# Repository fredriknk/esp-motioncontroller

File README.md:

# esp-motioncontroller

 <!-- 3D rendered pretty view -->

INFO INFO

[PCB layout](./DOCUMENTATION/esp-motioncontroller_board_prints.pdf) <!-- PDFs of boards -->
[SCHEMATIC](./DOCUMENTATION/esp-motioncontroller_schematic.pdf) <!-- Schematic PDFs -->

## FRONT

## BACK

## SIDE

# Before major commmits
Remember to run generate_outputs.bat/sh
to update the outputs and pictures.
readmetemplate

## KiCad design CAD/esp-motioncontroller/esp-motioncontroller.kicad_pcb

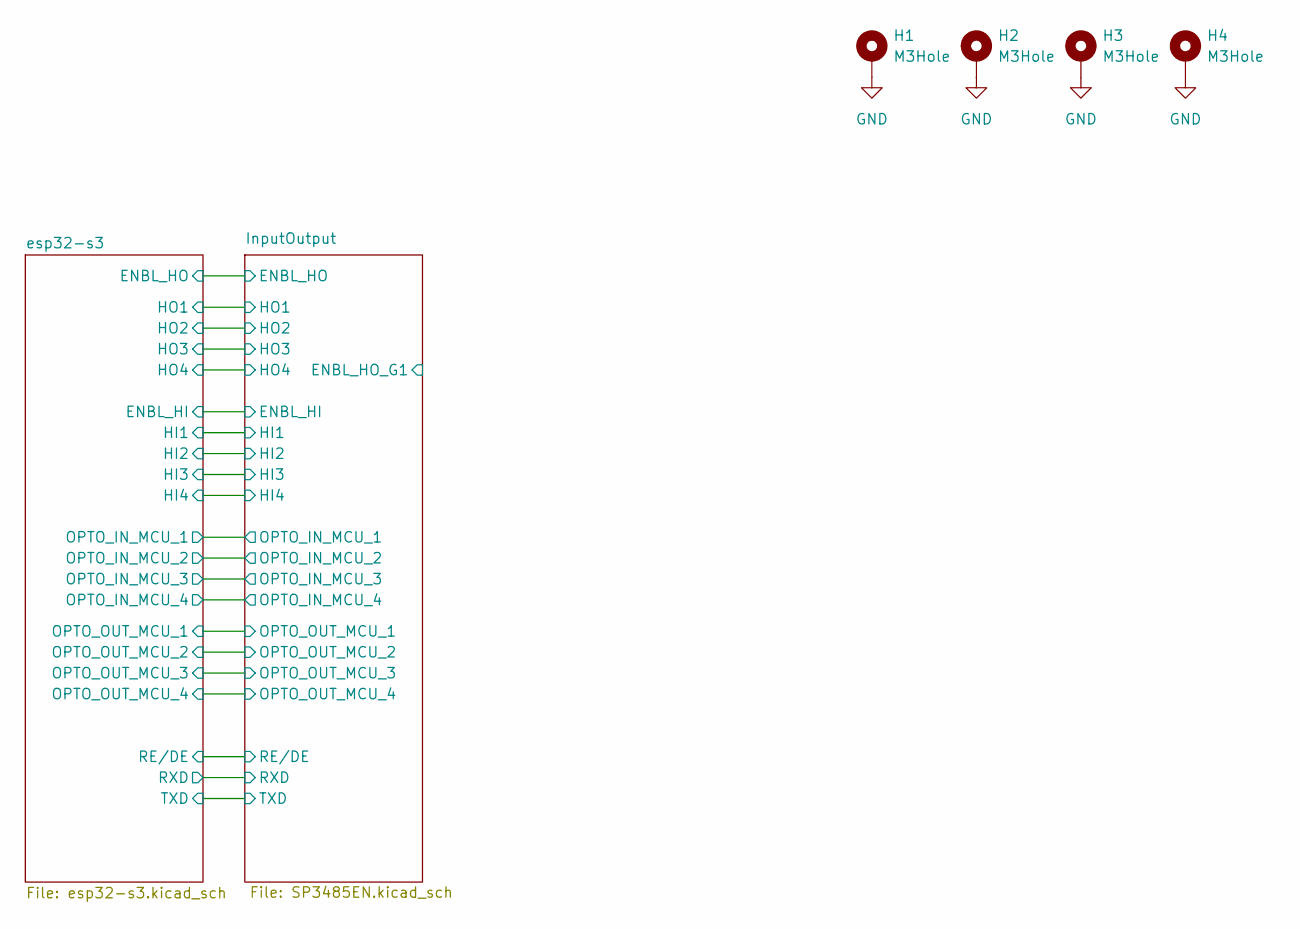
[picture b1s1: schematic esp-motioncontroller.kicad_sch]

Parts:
H1, H2, H3, H4: M3Hole; MountingHole_3.2mm_M3_DIN965_Pad

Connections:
GND: H1.1, H2.1, H3.1, H4.1; also elsewhere on the board

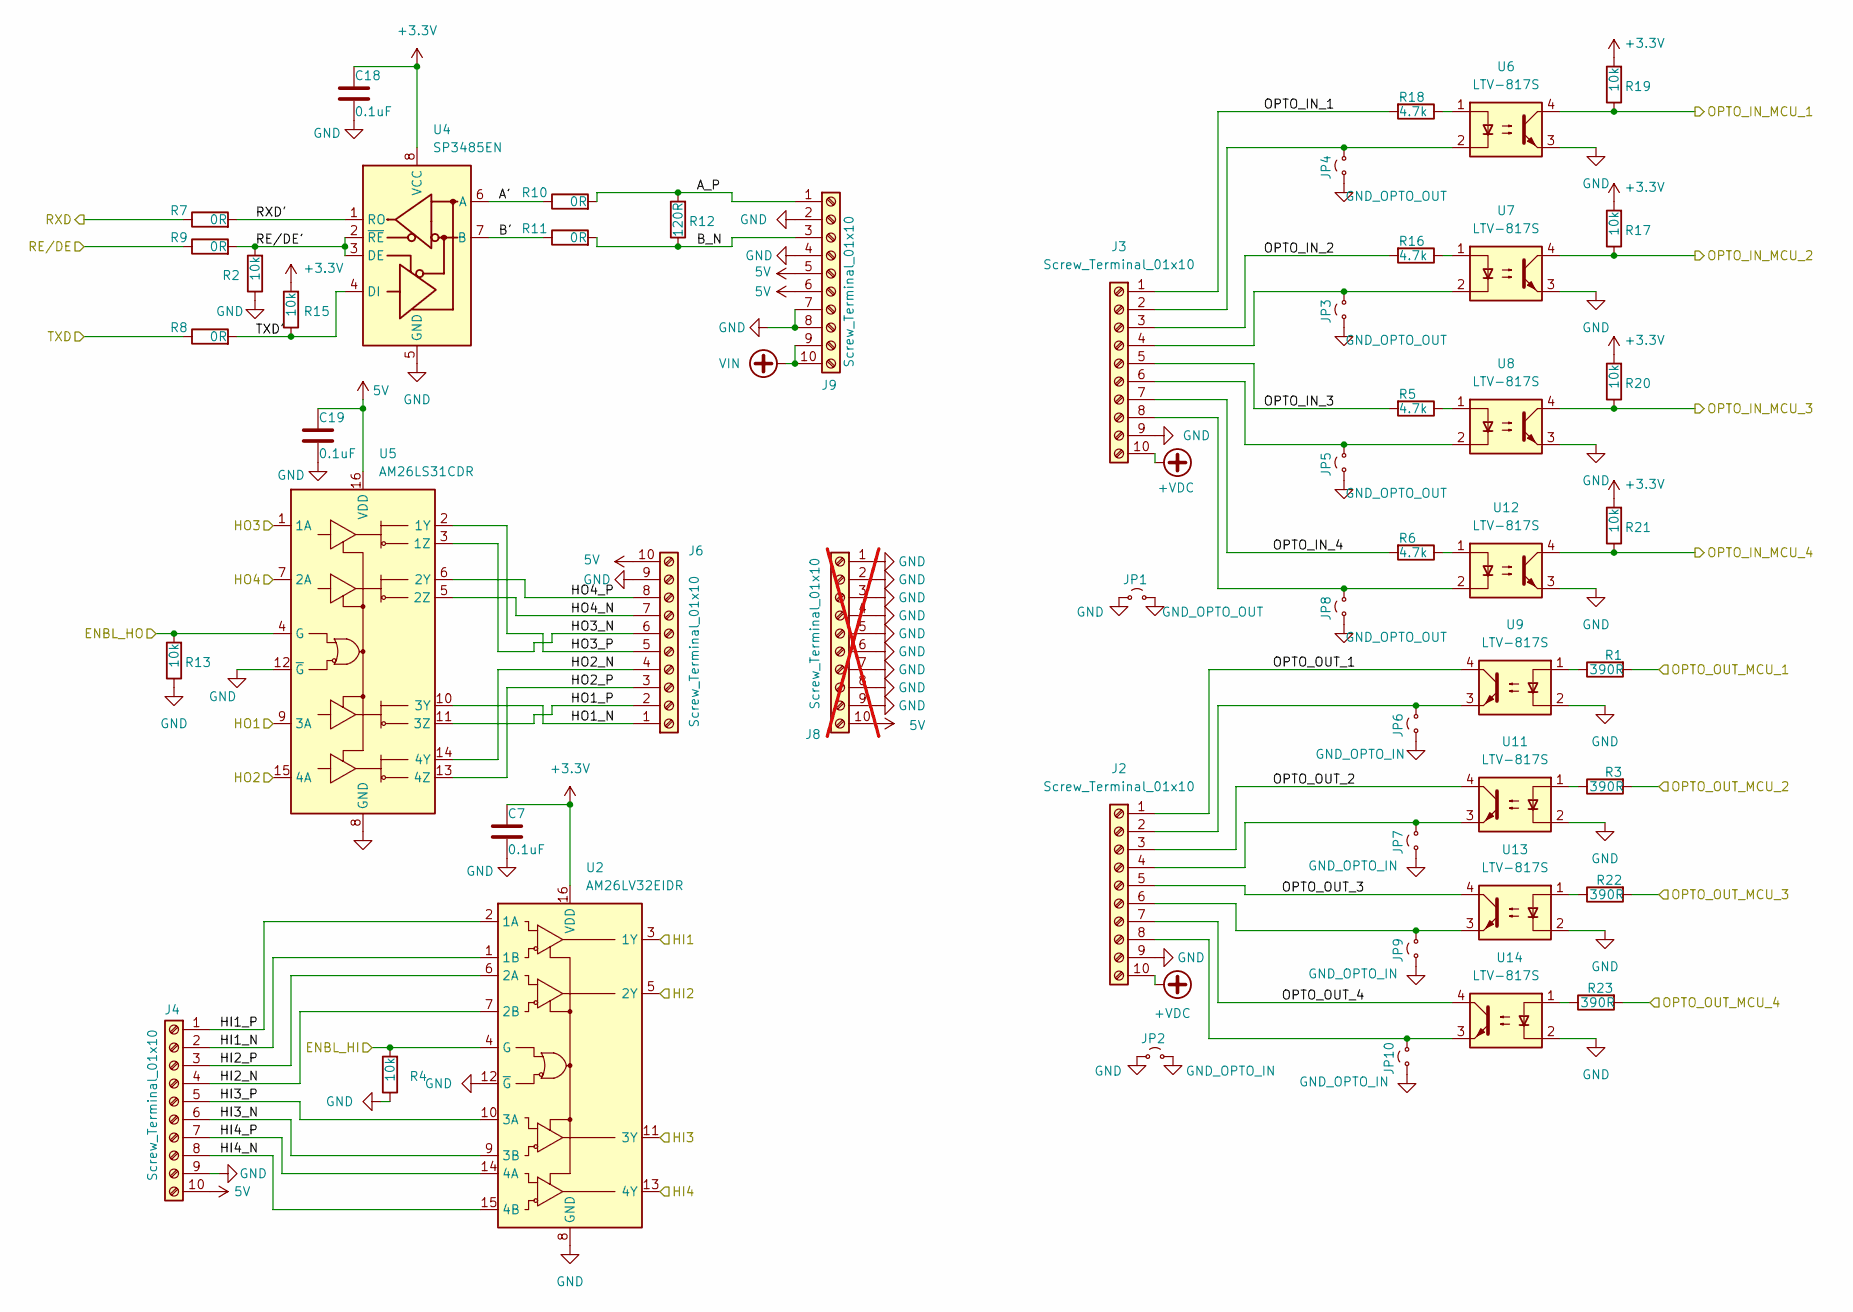
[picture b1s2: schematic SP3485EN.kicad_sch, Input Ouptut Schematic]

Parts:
C7, C18, C19: 0.1uF; C_0603_1608Metric; LCSC C14663
J2, J3, J4, J6, J9: Screw_Terminal_01x10; TerminalBlock_Phoenix_PT-1,5-10-3.5-H_1x10_P3.50mm_Horizont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; LCSC C5184956
J8: Screw_Terminal_01x10; TerminalBlock_Phoenix_PT-1,5-10-3.5-H_1x10_P3.50mm_Horizont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; LCSC C5184956; not fitted
JP1, JP2, JP3, JP4, JP5, JP6, JP7, JP8, JP9, JP10: Jumper_2_Small_Open; TestPoint_2Pads_Pitch2.54mm_Drill0.8mm
R1, R3, R22, R23: 390R; R_0603_1608Metric; LCSC C23151
R2, R4, R13, R15, R17, R19, R20, R21: 10k; R_0603_1608Metric; LCSC C25804
R5, R6, R16, R18: 4.7k; R_0603_1608Metric; LCSC C23162
R7, R8, R9, R10, R11: 0R; R_0603_1608Metric; LCSC C17477
R12: 120R; R_0603_1608Metric; LCSC C22787
U2: AM26LV32EIDR; SOIC-16_3.9x9.9mm_P1.27mm; LCSC C527448
U4: SP3485EN; SOIC-8_3.9x4.9mm_P1.27mm; LCSC C8963
U5: AM26LS31CDR; SOIC-16_3.9x9.9mm_P1.27mm; LCSC C6179
U6, U7, U8, U9, U11, U12, U13, U14: LTV-817S; SMDIP-4_W9.53mm; LCSC C109227

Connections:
5V: C19.1, J4.10, J6.10, J8.10, J9.5, J9.6, U5.16 (VDD); also elsewhere on the board
+3.3V: C7.1, C18.1, R15.2, R17.2, R19.2, R20.2, R21.2, U2.16 (VDD), U4.8 (VCC); also elsewhere on the board
+VDC: J2.10, J3.10; also elsewhere on the board
/InputOutput/A': R10.1, U4.6 (A)
/InputOutput/A_P: J9.1, R10.2, R12.2
/InputOutput/B': R11.1, U4.7 (B)
/InputOutput/B_N: J9.3, R11.2, R12.1
/InputOutput/ENBL_HI: R4.2, U2.4 (G); also elsewhere on the board
/InputOutput/ENBL_HO: R13.2, U5.4 (G); also elsewhere on the board
/InputOutput/HI1: U2.3 (1Y); also elsewhere on the board
/InputOutput/HI1_N: J4.2, U2.1 (1B)
/InputOutput/HI1_P: J4.1, U2.2 (1A)
/InputOutput/HI2: U2.5 (2Y); also elsewhere on the board
/InputOutput/HI2_N: J4.4, U2.7 (2B)
/InputOutput/HI2_P: J4.3, U2.6 (2A)
/InputOutput/HI3: U2.11 (3Y); also elsewhere on the board
/InputOutput/HI3_N: J4.6, U2.9 (3B)
/InputOutput/HI3_P: J4.5, U2.10 (3A)
/InputOutput/HI4: U2.13 (4Y); also elsewhere on the board
/InputOutput/HI4_N: J4.8, U2.15 (4B)
/InputOutput/HI4_P: J4.7, U2.14 (4A)
/InputOutput/HO1: U5.9 (3A); also elsewhere on the board
/InputOutput/HO1_N: J6.1, U5.10 (3Y)
/InputOutput/HO1_P: J6.2, U5.11 (3Z)
/InputOutput/HO2: U5.15 (4A); also elsewhere on the board
/InputOutput/HO2_N: J6.4, U5.14 (4Y)
/InputOutput/HO2_P: J6.3, U5.13 (4Z)
/InputOutput/HO3: U5.1 (1A); also elsewhere on the board
/InputOutput/HO3_N: J6.6, U5.3 (1Z)
/InputOutput/HO3_P: J6.5, U5.2 (1Y)
/InputOutput/HO4: U5.7 (2A); also elsewhere on the board
/InputOutput/HO4_N: J6.7, U5.5 (2Z)
/InputOutput/HO4_P: J6.8, U5.6 (2Y)
/InputOutput/OPTO_IN_1: J3.1, R18.2
/InputOutput/OPTO_IN_2: J3.3, R16.2
/InputOutput/OPTO_IN_3: J3.5, R5.2
/InputOutput/OPTO_IN_4: J3.7, R6.2
/InputOutput/OPTO_IN_MCU_1: R19.1, U6.4; also elsewhere on the board
/InputOutput/OPTO_IN_MCU_2: R17.1, U7.4; also elsewhere on the board
/InputOutput/OPTO_IN_MCU_3: R20.1, U8.4; also elsewhere on the board
/InputOutput/OPTO_IN_MCU_4: R21.1, U12.4; also elsewhere on the board
/InputOutput/OPTO_OUT_1: J2.1, U9.4
/InputOutput/OPTO_OUT_2: J2.3, U11.4
/InputOutput/OPTO_OUT_3: J2.5, U13.4
/InputOutput/OPTO_OUT_4: J2.7, U14.4
/InputOutput/OPTO_OUT_MCU_1: R1.2; also elsewhere on the board
/InputOutput/OPTO_OUT_MCU_2: R3.2; also elsewhere on the board
/InputOutput/OPTO_OUT_MCU_3: R22.2; also elsewhere on the board
/InputOutput/OPTO_OUT_MCU_4: R23.2; also elsewhere on the board
/InputOutput/RE/DE: R9.1; also elsewhere on the board
/InputOutput/RE/DE': R2.2, R9.2, U4.2 (~RE), U4.3 (DE)
/InputOutput/RXD: R7.1; also elsewhere on the board
/InputOutput/RXD': R7.2, U4.1 (RO)
/InputOutput/TXD: R8.1; also elsewhere on the board
/InputOutput/TXD': R8.2, R15.1, U4.4 (DI)
GND: C7.2, C18.2, C19.2, J2.9, J3.9, J4.9, J6.9, J8.1, J8.2, J8.3, J8.4, J8.5, J8.6, J8.7, J8.8, J8.9, J9.2, J9.4, J9.7, J9.8, JP1.1 (A), JP2.1 (A), R2.1, R4.1, R13.1, U2.8 (GND), U2.12 (~G), U4.5 (GND), U5.8 (GND), U5.12 (~G), U6.3, U7.3, U8.3, U9.2, U11.2, U12.3, U13.2, U14.2; also elsewhere on the board
GND_OPTO_IN: JP2.2 (B), JP6.1 (A), JP7.1 (A), JP9.1 (A), JP10.1 (A)
GND_OPTO_OUT: JP1.2 (B), JP3.1 (A), JP4.1 (A), JP5.1 (A), JP8.1 (A)
unnamed: J2.2, JP6.2 (B), U9.3
unnamed: J2.4, JP7.2 (B), U11.3
unnamed: J2.6, JP9.2 (B), U13.3
unnamed: J2.8, JP10.2 (B), U14.3
unnamed: J3.2, JP4.2 (B), U6.2
unnamed: J3.4, JP3.2 (B), U7.2
unnamed: J3.6, JP5.2 (B), U8.2
unnamed: J3.8, JP8.2 (B), U12.2
unnamed: R1.1, U9.1
unnamed: R3.1, U11.1
unnamed: R5.1, U8.1
unnamed: R6.1, U12.1
unnamed: R16.1, U7.1
unnamed: R18.1, U6.1
unnamed: R22.1, U13.1
unnamed: R23.1, U14.1
VIN: J9.9, J9.10; also elsewhere on the board

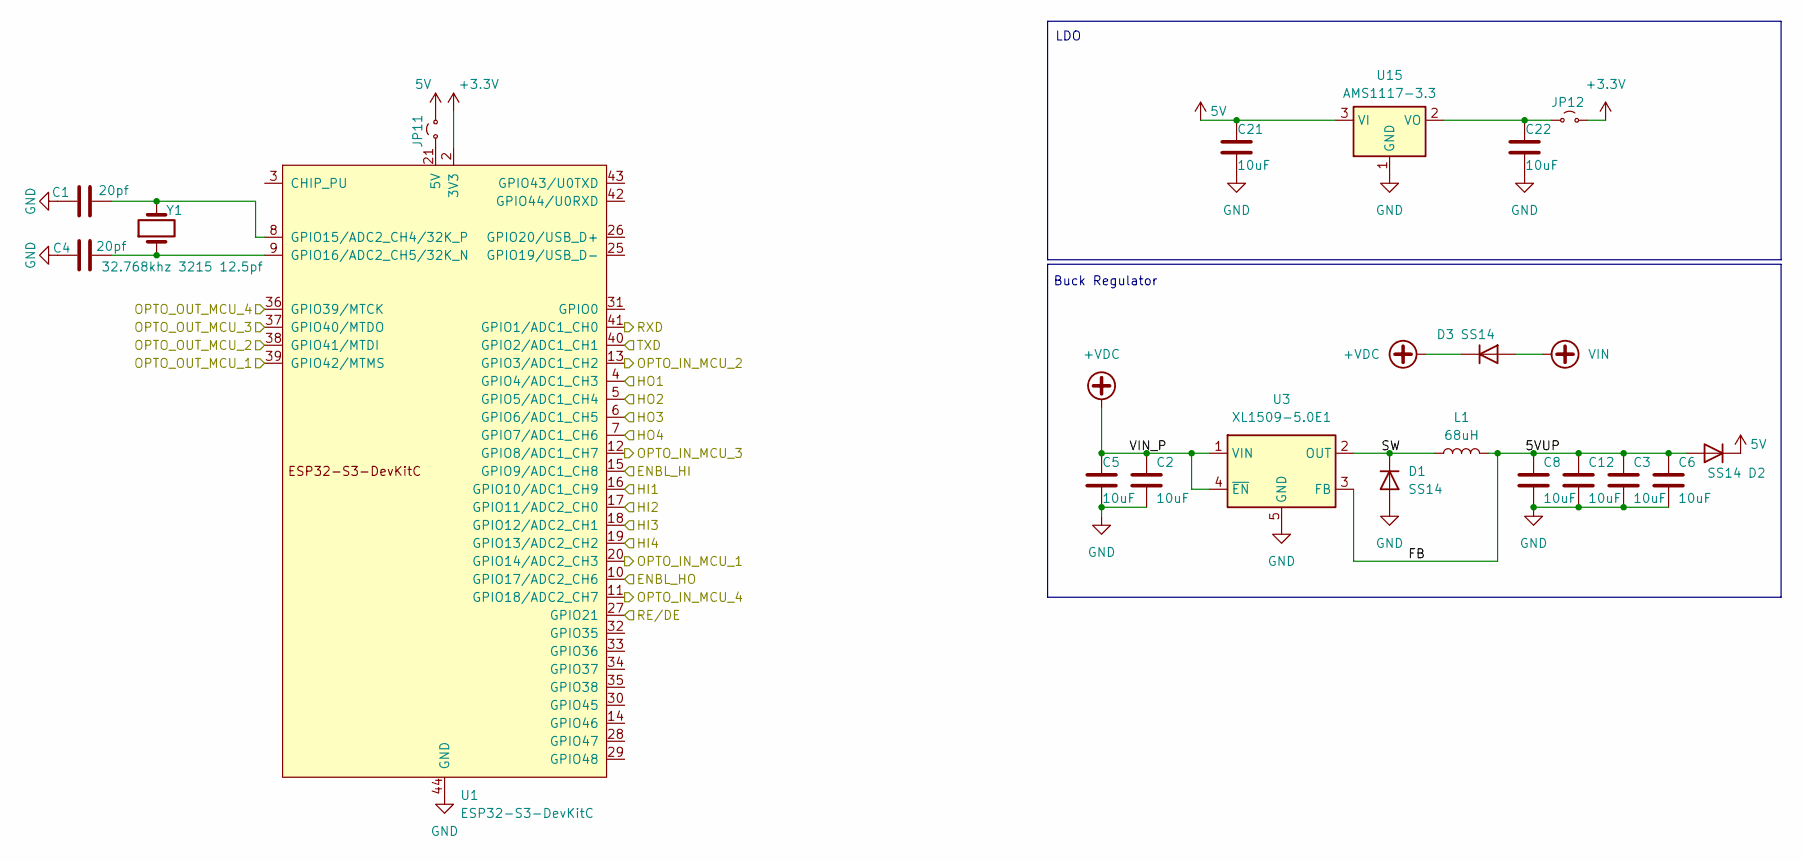
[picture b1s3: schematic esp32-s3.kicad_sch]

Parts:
C1, C4: 20pf; R_0603_1608Metric; LCSC C1648
C2, C3, C5, C6, C8, C12, C21, C22: 10uF; C_1206_3216Metric; LCSC C13585
D1, D2, D3: SS14; D_SMA; LCSC C2480
JP11, JP12: Jumper_2_Small_Open; TestPoint_2Pads_Pitch2.54mm_Drill0.8mm
L1: 68uH; L_SOREDE_SNR.1050_10x10x5mm; LCSC C9187
U1: ESP32-S3-DevKitC
U3: XL1509-5.0E1; SOIC-8_3.9x4.9mm_P1.27mm; LCSC C61063
U15: AMS1117-3.3; SOT-223-3_TabPin2; LCSC C6186
Y1: 32.768khz 3215 12.5pf; Crystal_SMD_3215-2Pin_3.2x1.5mm; LCSC C32346

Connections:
5V: C21.1, D2.1 (K), JP11.2 (B), U15.3 (VI); also elsewhere on the board
+3.3V: JP12.2 (B), U1.1 (3V3), U1.2 (3V3); also elsewhere on the board
+VDC: C2.1, C5.1, D3.1 (K), U3.1 (VIN), U3.4 (~EN); also elsewhere on the board
/InputOutput/ENBL_HI: U1.15 (GPIO9/ADC1_CH8); also elsewhere on the board
/InputOutput/ENBL_HO: U1.10 (GPIO17/ADC2_CH6); also elsewhere on the board
/InputOutput/HI1: U1.16 (GPIO10/ADC1_CH9); also elsewhere on the board
/InputOutput/HI2: U1.17 (GPIO11/ADC2_CH0); also elsewhere on the board
/InputOutput/HI3: U1.18 (GPIO12/ADC2_CH1); also elsewhere on the board
/InputOutput/HI4: U1.19 (GPIO13/ADC2_CH2); also elsewhere on the board
/InputOutput/HO1: U1.4 (GPIO4/ADC1_CH3); also elsewhere on the board
/InputOutput/HO2: U1.5 (GPIO5/ADC1_CH4); also elsewhere on the board
/InputOutput/HO3: U1.6 (GPIO6/ADC1_CH5); also elsewhere on the board
/InputOutput/HO4: U1.7 (GPIO7/ADC1_CH6); also elsewhere on the board
/InputOutput/OPTO_IN_MCU_1: U1.20 (GPIO14/ADC2_CH3); also elsewhere on the board
/InputOutput/OPTO_IN_MCU_2: U1.13 (GPIO3/ADC1_CH2); also elsewhere on the board
/InputOutput/OPTO_IN_MCU_3: U1.12 (GPIO8/ADC1_CH7); also elsewhere on the board
/InputOutput/OPTO_IN_MCU_4: U1.11 (GPIO18/ADC2_CH7); also elsewhere on the board
/InputOutput/OPTO_OUT_MCU_1: U1.39 (GPIO42/MTMS); also elsewhere on the board
/InputOutput/OPTO_OUT_MCU_2: U1.38 (GPIO41/MTDI); also elsewhere on the board
/InputOutput/OPTO_OUT_MCU_3: U1.37 (GPIO40/MTDO); also elsewhere on the board
/InputOutput/OPTO_OUT_MCU_4: U1.36 (GPIO39/MTCK); also elsewhere on the board
/InputOutput/RE/DE: U1.27 (GPIO21); also elsewhere on the board
/InputOutput/RXD: U1.41 (GPIO1/ADC1_CH0); also elsewhere on the board
/InputOutput/TXD: U1.40 (GPIO2/ADC1_CH1); also elsewhere on the board
/esp32-s3/5VUP: C3.1, C6.1, C8.1, C12.1, D2.2 (A), L1.2, U3.3 (FB)
/esp32-s3/SW: D1.1 (K), L1.1, U3.2 (OUT)
GND: C1.1, C2.2, C3.2, C4.2, C5.2, C6.2, C8.2, C12.2, C21.2, C22.2, D1.2 (A), U1.22 (GND), U1.23 (GND), U1.24 (GND), U1.44 (GND), U3.5 (GND), U3.6 (GND), U3.7 (GND), U3.8 (GND), U15.1 (GND); also elsewhere on the board
unnamed: JP11.1 (A), U1.21 (5V)
unnamed: C22.1, JP12.1 (A), U15.2 (VO)
unnamed: C1.2, U1.8 (GPIO15/ADC2_CH4/32K_P), Y1.2
unnamed: C4.1, U1.9 (GPIO16/ADC2_CH5/32K_N), Y1.1
VIN: D3.2 (A); also elsewhere on the board

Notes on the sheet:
Buck Regulator
LDO

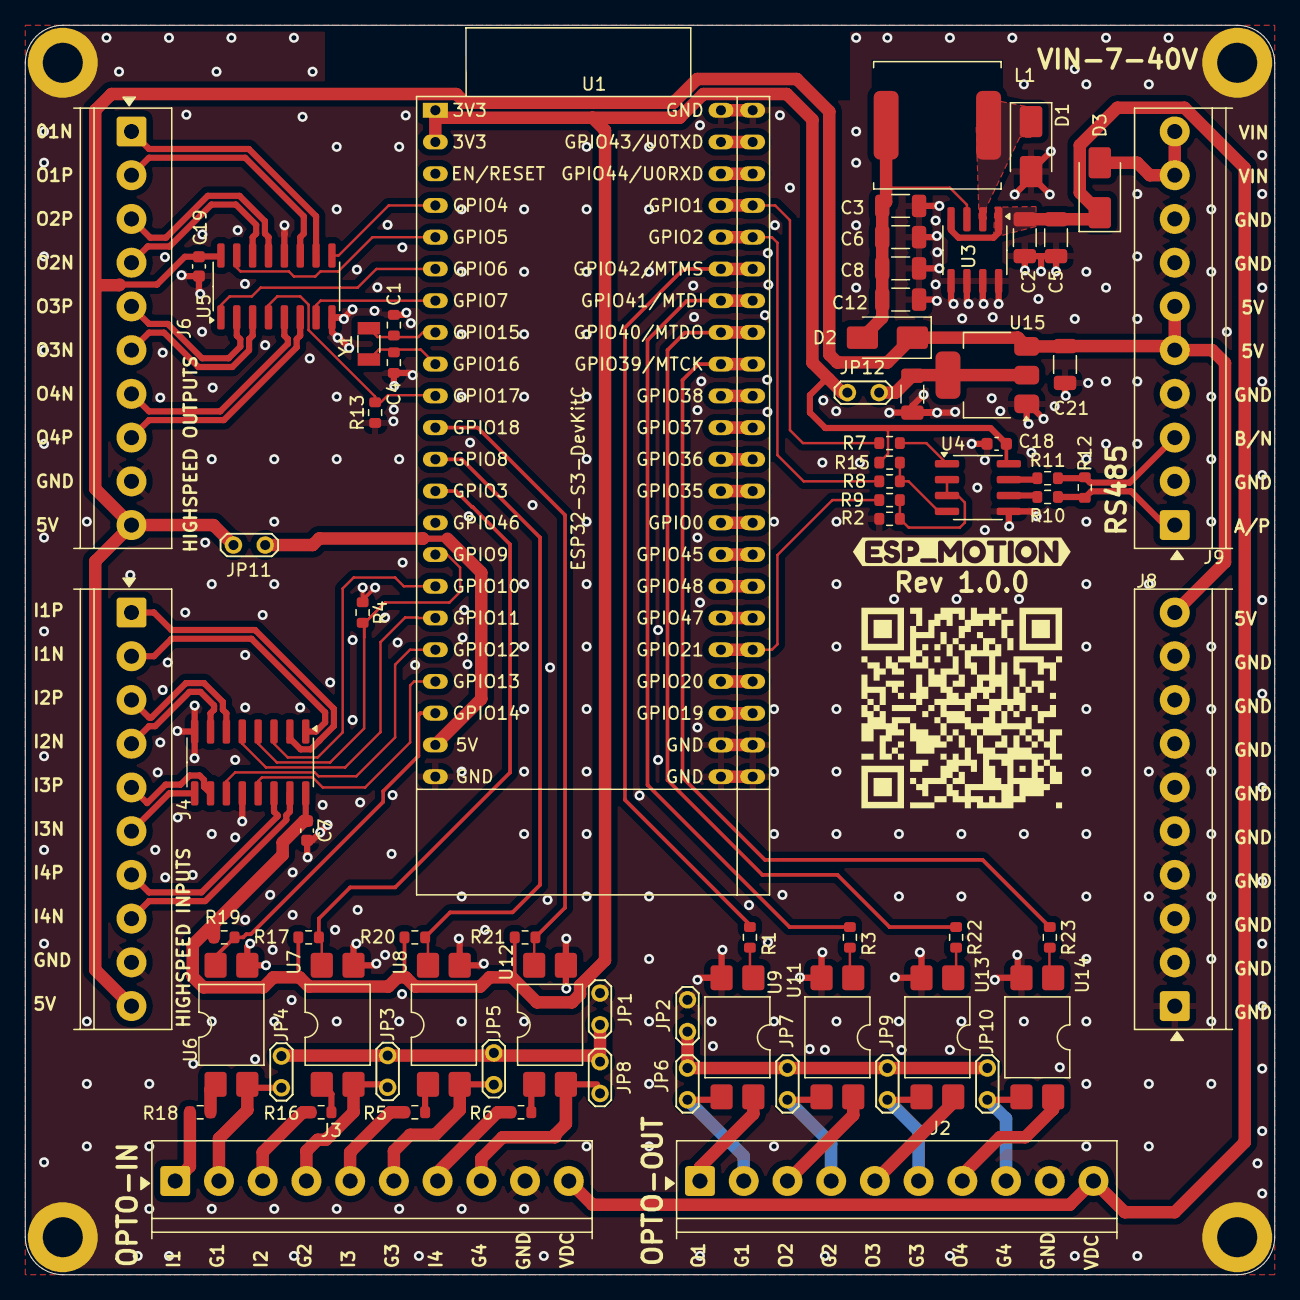
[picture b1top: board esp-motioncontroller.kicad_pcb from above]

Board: 2 copper layers, 100.0 x 100.0 mm, 77 parts (0 on the bottom side), 81 nets.

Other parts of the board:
kibuzzard-6890605B: G***; kibuzzard-6890605B

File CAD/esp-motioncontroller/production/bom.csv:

Designator,Footprint,Quantity,Value,LCSC Part #
"C1, C4",0603,2,20pf,C1648
"C12, C2, C21, C22, C3, C5, C6, C8",1206,8,10uF,C13585
"C18, C19, C7",0603,3,0.1uF,C14663
"D1, D2, D3",D_SMA,3,SS14,C2480
J1,PinHeader_1x06_P2.54mm_Vertical,1,Conn_01x06,
"J2, J3, J4, J6, J9","TerminalBlock_Phoenix_PT-1,5-10-3.5-H_1x10_P3.50mm_Horizontal",5,Screw_Terminal_01x10,C5184956
L1,L_SOREDE_SNR.1050_10x10x5mm,1,68uH,C9187
"R1, R22, R23, R3",0603,4,390R,C23151
"R10, R11, R7, R8, R9",0603,5,0R,C17477
R12,0603,1,120R,C22787
"R13, R15, R17, R19, R2, R20, R21, R4",0603,8,10k,C25804
"R16, R18, R5, R6",0603,4,4.7k,C23162
"U11, U12, U13, U14, U6, U7, U8, U9",SMDIP-4_W9.53mm,8,LTV-817S,C109227
U15,SOT-223-3_TabPin2,1,AMS1117-3.3,C6186
U2,SOIC-16_3.9x9.9mm_P1.27mm,1,AM26LV32EIDR,C527448
U3,SOIC-8_3.9x4.9mm_P1.27mm,1,XL1509-5.0E1,C61063
U4,SOIC-8_3.9x4.9mm_P1.27mm,1,SP3485EN,C8963
U5,SOIC-16_3.9x9.9mm_P1.27mm,1,AM26LS31CDR,C6179
Y1,Crystal_SMD_3215-2Pin_3.2x1.5mm,1,32.768khz 3215 12.5pf,C32346

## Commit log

2025-07-30 Feat: First Push
2025-07-30 Feat: WIP Adding Differential input
2025-07-31 Feat: Additional driver
2025-07-31 Feat: 485 single drivers
2025-07-31 Feat: Allmost complete sepdriver
2025-08-01 Fix: Lockremove
2025-08-01 Feat: Quaddrivers
2025-08-04 Feat: Local libs, more devboards
2025-08-04 Feat: Fixed CI vendor prod files, and auto readme generation
2025-08-04 Feat: Working quaddriver and CI
2025-08-04 Fix: Pulled sch changes
2025-08-04 Feat: Ran CI
